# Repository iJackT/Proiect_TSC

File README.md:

OpenBook E-book Reader

Urmatorul fisier contine detalii despre implmentarea proiectului

Descriere generala
OpenBook este un e-reader open-source construit pe baza unui controller ESP32-C6. Acesta se foloseste de un ecran de 7.5" dar nu numai.

Diagrama Bloc:

Componente importante:

Microcontroller – ESP32-C6-WROOM-1
CPU: RISC-V pe 32 de biți, frecvență de 160 MHz
Memorie: 512 KB SRAM + 8 MB flash extern (model W25Q512JVEIQ)
Conectivitate: Suportă Wi-Fi 6 (802.11ax), Bluetooth 5 Low Energy, USB 2.0 Full-Speed

Ecran E-Ink – Waveshare WSH-13187, 7.5”
Rezoluție afișaj: 800x480 pixeli, alb-negru
Comunicare: Interfață SPI cu fire dedicate CS, DC, RST, BUSY
Consum de curent: Între 15–25 mA la reîmprospătare, consum nul în stare statică

Senzor ambiental – Bosch BME688
Măsurători: Temperatură, umiditate, presiune, calitate aer (eCO2, TVOC)
Precizie: ±1 °C (temperatură), ±3% (umiditate), ±1 hPa (presiune)
Comunicare: Protocol I²C @ 400 kHz

Alimentare și gestiunea energiei
Baterie: Li-Po 3.7V, capacitate 2500 mAh
Monitorizare baterie: MAX17048 (interfață I²C)
Încărcare: MCP73831, input 5V/1A prin conector USB-C

Interfață butoane – 3x switch tactil
Tip: Panasonic EVQ-Q2A03W
Legătură: GPIO cu debounce hardware (filtru RC)
Utilizare: Navigare în meniu, derulare pagini, confirmare acțiuni

Conector USB-C
Funcții: Încărcare baterie și transfer de date prin USB 2.0
Protecții: ESD și rezistențe de terminare corect configurate
Capabilități adiționale: Suport actualizări firmware prin USB și OTA prin Wi-Fi

Conector rapid I²C – Qwiic / STEMMA QT
Pini: VCC, GND, SDA, SCL
Rol: Permite conectarea ușoară a modulelor și senzorilor compatibili I²C

Slot MicroSD – Attend 112A-TAAR-R03
Scop: Permite stocarea externă de fișiere (cărți, jurnale, firmware)
Interfață: Conectare prin SPI

Ceas de timp real (RTC) – DS3231
Precizie: ±2 ppm
Interfață: I²C
Backup: Alimentare de rezervă prin supercapacitor

Pini folositi

| Pin ESP32-C6 | Componentă / Semnal                | De ce?                                                                 |
|--------------|-------------------------------------|------------------------------------------------------------------------|
| GPIO1        | I²C SDA (BME688, MAX17048, DS3231, Qwiic) | Linie partajată I²C – economisește pini și permite extinderea facilă |
| GPIO2        | I²C SCL (BME688, MAX17048, DS3231, Qwiic) | Clock I²C pentru toți senzorii și extensii Qwiic                     |
| GPIO5        | SPI MISO (E-Paper, Flash extern)    | Linie comună de intrare date în SPI                                   |
| GPIO6        | SPI MOSI (E-Paper, Flash extern)    | Linie de ieșire date către e-paper și flash                           |
| GPIO7        | SPI CLK                             | Semnal de clock pentru magistrala SPI                                 |
| GPIO8        | E-Paper CS                          | Selectează afișajul pe magistrala SPI                                 |
| GPIO9        | E-Paper DC (Data/Command)           | Comută între comandă și date către e-paper                            |
| GPIO10       | E-Paper RST                         | Reset hardware e-paper                                                |
| GPIO11       | E-Paper BUSY                        | Pin de stare (ocupat/liber) de la display                             |
| GPIO12       | Button #1                           | Intrare digitală pentru navigare pagină înainte                      |
| GPIO13       | Button #2                           | Intrare digitală pentru navigare pagină înapoi                       |
| GPIO14       | Button #3                           | Intrare digitală pentru selectare/opțiune                            |
| GPIO15       | MAX17048 ALERT (opțional)           | Pin de alertă nivel scăzut baterie                                    |
| GPIO16       | USB D+ (intern la USB PHY)          | Linie USB 2.0 (fixă pe ESP32-C6)                                      |
| GPIO17       | USB D- (intern la USB PHY)          | Linie USB 2.0 (fixă pe ESP32-C6)                                      |
| GPIO18       | LED Status (opțional)               | Indicator pentru activitate Wi-Fi, charging, notificări               |
| GPIO19       | SD Card CS                          | Selectare chip pentru card microSD (SPI)                              |
| GPIO20       | SD Card MISO                        | Citire date de pe card microSD                                        |
| GPIO21       | SD Card MOSI                        | Scriere date pe card microSD                                          |
| GPIO4        | SD Card CLK                         | Semnal de clock pentru card microSD (SPI)                             |

Comunicatii si Interfete

| Tip       | Componente                                          |
|-----------|-----------------------------------------------------|
| **SPI**   | E-Paper, Flash extern, SD Card (în mod SPI)         |
| **I²C**   | BME688, MAX17048, DS3231, Qwiic/Stemma              |
| **USB**   | Încărcare și transfer date prin USB-C               |
| **GPIO**  | Butoane, semnale control afișaj, charging enable    |

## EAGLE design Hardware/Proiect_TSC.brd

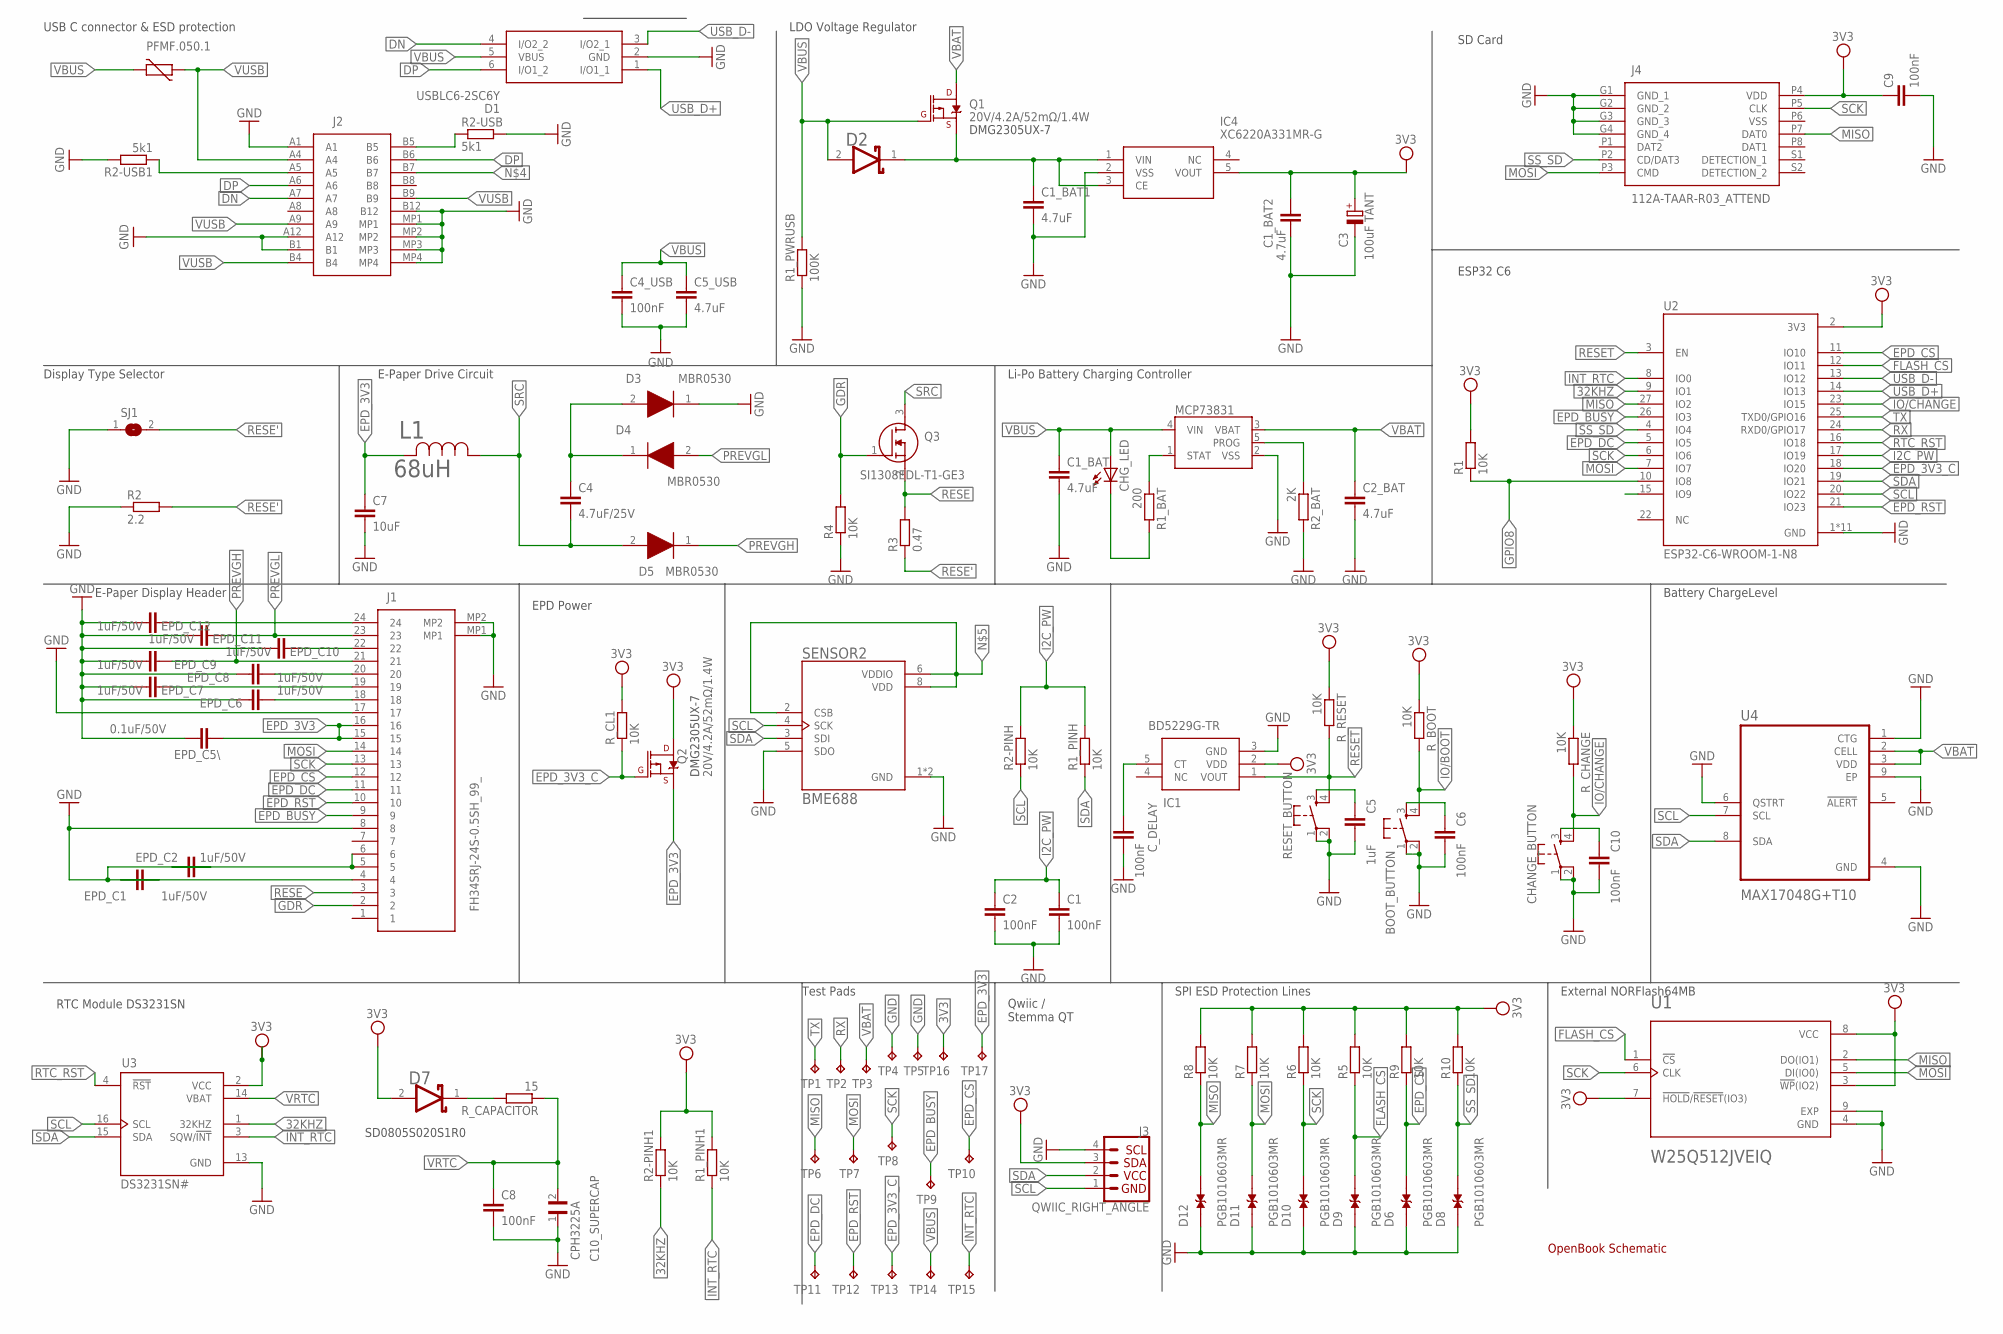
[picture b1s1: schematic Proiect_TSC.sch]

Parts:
BOOT_BUTTON: BUTTON_CUSYOMV1; MYBUTTON
C1, C2, C4_USB, C6, C8, C9, C10: 100nF; ESP32_WROVER_EAGLE-LTSPICE_C0402
C1_BAT, C1_BAT1, C1_BAT2, C2_BAT, C5_USB: 4.7uF; ESP32_WROVER_EAGLE-LTSPICE_C0402
C3: 100uF TANT; RCL_CT3528
C4: 4.7uF/25V; ESP32_WROVER_EAGLE-LTSPICE_C0402
C5: 1uF; ESP32_WROVER_EAGLE-LTSPICE_C0402
C7: 10uF; ESP32_WROVER_EAGLE-LTSPICE_C0402
C10_SUPERCAP: CPH3225A; CAPCP3225X100N
CHANGE_BUTTON: BUTTON_CUSYOMV1; MYBUTTON
CHG_LED: ADAFRUIT_LEDCHIP-LED0603; ADAFRUIT_CHIP-LED0603
C_DELAY: 100nF; ESP32_WROVER_EAGLE-LTSPICE_C0402
D1: USBLC6-2SC6Y; SOT95P280X145-6N
D2, D7: ESP32_WROVER_AVX---SD0805S020S1R0_AVX_SD0805S020S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; ESP32_WROVER_AVX---SD0805S020S1R0_AVX_SD0805S020S1R0_0
D3, D4, D5: MBR0530; SOD3716X135N
D6, D8, D9, D10, D11, D12: PGB1010603MR; DIOC1608X36N
EPD_C1, EPD_C2: 1uF/50V; ESP32_WROVER_EAGLE-LTSPICE_C0402
EPD_C5\: 0.1uF/50V; EAGLE-LTSPICE_C0402
EPD_C6, EPD_C7, EPD_C8, EPD_C9, EPD_C10, EPD_C11, EPD_C12: 1uF/50V; EAGLE-LTSPICE_C0402
IC1: BD5229G-TR; SOT95P280X125-5N
IC4: XC6220A331MR-G; SOT95P280X120-5N
J1: FH34SRJ-24S-0.5SH_99_; FH34SRJ24S05SH99
J2: SAMACSYS_PARTS_USB4110-GF-A; SAMACSYS_PARTS_USB4110GFA
J3: QWIIC_RIGHT_ANGLE; JST04_1MM_RA
J4: 112A-TAAR-R03_ATTEND; 112ATAARR03ATTEND
L1: 68uH; IND_4828-WE-TPC_WRE
MCP73831: ESP32_WROVER_SPARKFUN-IC-POWER_MCP73831; ESP32_WROVER_SPARKFUN-IC-POWER_SOT23-5
PFMF.050.1: ESP32C6_VARISTORCN1812; ESP32C6_VARISTOR_CT/CN1812
Q1, Q2: 20V/4.2A/52mΩ/1.4W; ESP32_WROVER_SPARKFUN-DISCRETESEMI_SOT23-3
Q3: SI1308EDL-T1-GE3; SOT65P210X110-3N
R1, R1_PINH, R1_PINH1, R2-PINH, R2-PINH1, R4, R5, R6, R7, R8, R9, R10: 10K; ESP32_WROVER_EAGLE-LTSPICE_R0402
R1_BAT: 200; ESP32_WROVER_EAGLE-LTSPICE_R0402
R1_PWRUSB: 100K; ESP32_WROVER_EAGLE-LTSPICE_R0402
R2: 2.2; ESP32_WROVER_EAGLE-LTSPICE_R0402
R2-USB, R2-USB1: 5k1; ESP32_WROVER_EAGLE-LTSPICE_R0402
R2_BAT: 2K; ESP32_WROVER_EAGLE-LTSPICE_R0402
R3: 0.47; ESP32_WROVER_EAGLE-LTSPICE_R0402
RESET_BUTTON: BUTTON_CUSYOMV1; MYBUTTON
R_BOOT: 10K; ESP32_WROVER_EAGLE-LTSPICE_R0402
R_CAPACITOR: 15; ESP32_WROVER_EAGLE-LTSPICE_R0402
R_CHANGE: 10K; ESP32_WROVER_EAGLE-LTSPICE_R0402
R_CL1: 10K; ESP32_WROVER_EAGLE-LTSPICE_R0402
R_RESET: 10K; ESP32_WROVER_EAGLE-LTSPICE_R0402
SENSOR2: BME688; ESP32_WROVER_BME680_PSON80P300X300X100-8N
SJ1: SJ
TP1, TP2, TP3, TP4, TP5, TP6, TP7, TP8, TP9, TP10, TP11, TP12, TP13, TP14, TP15, TP16, TP17: TPTP20R; TP20R
U1: W25Q512JVEIQ; SON127P600X800X80-9N
U2: ESP32-C6-WROOM-1-N8; XCVR_ESP32-C6-WROOM-1-N8
U3: DS3231SN#; SOIC127P1032X265-16N
U4: MAX17048G+T10; SON50P200X200X80-9N

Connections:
3V3: C1_BAT2.1, C3.+, C9.1, D7.2 (ANODE), IC1.2 (VDD), IC4.5 (VOUT), J3.3, J4.P4 (VDD), Q2.3 (D), R1.2, R1_PINH1.2, R2-PINH1.2, R5.2, R6.2, R7.2, R8.2, R9.2, R10.2, R_BOOT.1, R_CHANGE.1, R_CL1.2, R_RESET.1, TP16.TP, U1.3 (!WP!(IO2)), U1.7 (!HOLD!/!RESET!(IO3)), U1.8 (VCC), U2.2 (3V3), U3.2 (VCC)
32KHZ: R2-PINH1.1, U2.9 (IO1), U3.1 (32KHZ)
DN: D1.4 (I/O2_2), J2.A7
DP: D1.6 (I/O1_2), J2.A6, J2.B6
EPD_3V3: C7.1, EPD_C5\.1, J1.15, J1.16, L1.2, Q2.2 (S), TP17.TP
EPD_3V3_C: Q2.1 (G), R_CL1.1, TP13.TP, U2.18 (IO20)
EPD_BUSY: J1.9, TP9.TP, U2.26 (IO3)
EPD_C2: EPD_C2.2, J1.5, J1.6
EPD_CS: D6.2, J1.12, R9.1, TP10.TP, U2.11 (IO10)
EPD_DC: J1.11, TP11.TP, U2.5 (IO5)
EPD_RST: J1.10, TP12.TP, U2.21 (IO23)
FLASH_CS: D9.2, R5.1, U1.1 (!CS), U2.12 (IO11)
GDR: J1.2, Q3.1 (G), R4.2
GND: BOOT_BUTTON.2, C1.2, C1_BAT.2, C1_BAT1.2, C1_BAT2.2, C2.2, C2_BAT.2, C3.-, C4_USB.2, C5.2, C5_USB.2, C6.2, C7.2, C8.2, C9.2, C10.2, C10_SUPERCAP.1, CHANGE_BUTTON.2, C_DELAY.2, D1.2 (GND), D3.1 (K), D6.1, D8.1, D9.1, D10.1, D11.1, D12.1, EPD_C1.1, EPD_C2.1, EPD_C5\.2, EPD_C6.2, EPD_C7.2, EPD_C8.2, EPD_C9.2, EPD_C10.2, EPD_C11.2, EPD_C12.2, IC1.3 (GND), IC4.2 (VSS), J1.8, J1.17, J1.MP1, J1.MP2, J2.A1, J2.A12, J2.B1, J2.B12, J2.MP1, J2.MP2, J2.MP3, J2.MP4, J3.4, J4.G1 (GND_1), J4.G2 (GND_2), J4.G3 (GND_3), J4.G4 (GND_4), MCP73831.2 (VSS), R1_PWRUSB.1, R2.1, R2-USB.2, R2-USB1.2, R2_BAT.2, R4.1, RESET_BUTTON.1, RESET_BUTTON.2, SENSOR2.1 (GND), SENSOR2.5 (SDO), SENSOR2.7 (GND), SJ1.1, TP4.TP, TP5.TP, U1.4 (GND), U1.9 (EXP), U2.1 (GND), U2.28 (GND), U2.29_1 (GND), U2.29_2 (GND), U2.29_3 (GND), U2.29_4 (GND), U2.29_5 (GND), U2.29_6 (GND), U2.29_7 (GND), U2.29_8 (GND), U2.29_9 (GND), U3.13 (GND), U4.1 (CTG), U4.4 (GND), U4.6 (QSTRT), U4.9 (EP)
GPIO8: R1.1, U2.10 (IO8)
I2C_PW: C1.1, C2.1, R1_PINH.2, R2-PINH.2, U2.17 (IO19)
INT_RTC: R1_PINH1.1, TP15.TP, U2.8 (IO0), U3.3 (SQW/!INT)
IO/BOOT: BOOT_BUTTON.4, R_BOOT.2
IO/CHANGE: CHANGE_BUTTON.4, R_CHANGE.2, U2.23 (IO15)
MISO: D12.2, J4.P7 (DAT0), R8.1, TP6.TP, U1.2 (DO(IO1)), U2.27 (IO2)
MOSI: D11.2, J1.14, J4.P3 (CMD), R7.1, TP7.TP, U1.5 (DI(IO0)), U2.7 (IO7)
unnamed: J2.A5, R2-USB1.1
unnamed: J2.B5, R2-USB.1
unnamed: C1_BAT1.1, D2.1 (CATHODE), IC4.1 (VIN), IC4.3 (CE), Q1.2 (S)
unnamed: SENSOR2.2 (CSB), SENSOR2.6 (VDDIO), SENSOR2.8 (VDD)
unnamed: MCP73831.5 (PROG), R2_BAT.1
unnamed: C4.1, D3.2 (A), D4.1 (K)
unnamed: C_DELAY.1, IC1.5 (CT)
unnamed: EPD_C1.2, J1.4
unnamed: MCP73831.1 (STAT), R1_BAT.1
unnamed: CHG_LED.C, R1_BAT.2
unnamed: EPD_C6.1, J1.18
unnamed: EPD_C7.1, J1.19
unnamed: EPD_C8.1, J1.20
unnamed: D7.1 (CATHODE), R_CAPACITOR.2
unnamed: EPD_C10.1, J1.22
unnamed: BOOT_BUTTON.3, C6.1
unnamed: EPD_C12.1, J1.24
unnamed: C5.1, RESET_BUTTON.3
unnamed: C10.1, CHANGE_BUTTON.3
PREVGH: D5.1 (K), EPD_C9.1, J1.21
PREVGL: D4.2 (A), EPD_C11.1, J1.23
RESE: J1.3, Q3.2 (S), R3.2
RESE': R2.2, R3.1, SJ1.2
RESET: IC1.1 (VOUT), RESET_BUTTON.4, R_RESET.2, U2.3 (EN)
RTC_RST: U2.16 (IO18), U3.4 (!RST)
RX: TP2.TP, U2.24 (RXD0/GPIO17)
SCK: D10.2, J1.13, J4.P5 (CLK), R6.1, TP8.TP, U1.6 (CLK), U2.6 (IO6)
SCL: J3.1, R2-PINH.1, SENSOR2.4 (SCK), U2.20 (IO22), U3.16 (SCL), U4.7 (SCL)
SDA: J3.2, R1_PINH.1, SENSOR2.3 (SDI), U2.19 (IO21), U3.15 (SDA), U4.8 (SDA)
SRC: C4.2, D5.2 (A), L1.1, Q3.3 (D)
SS_SD: D8.2, J4.P2 (CD/DAT3), R10.1, U2.4 (IO4)
TX: TP1.TP, U2.25 (TXD0/GPIO16)
USB_D+: D1.1 (I/O1_1), U2.14 (IO13)
USB_D-: D1.3 (I/O2_1), U2.13 (IO12)
VBAT: C2_BAT.1, MCP73831.3 (VBAT), Q1.3 (D), TP3.TP, U4.2 (CELL), U4.3 (VDD)
VBUS: C1_BAT.1, C4_USB.1, C5_USB.1, CHG_LED.A, D1.5 (VBUS), D2.2 (ANODE), MCP73831.4 (VIN), PFMF.050.1.2, Q1.1 (G), R1_PWRUSB.2, TP14.TP
VRTC: C8.1, C10_SUPERCAP.2, R_CAPACITOR.1, U3.14 (VBAT)
VUSB: J2.A4, J2.A9, J2.B4, J2.B9, PFMF.050.1.1

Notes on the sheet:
USB C connector & ESD protection
DMG2305UX-7
LDO Voltage Regulator
SD Card
Display Type Selector
E-Paper Drive Circuit
Li-Po Battery Charging Controller
ESP32 C6
EPD Power
Battery ChargeLevel
E-Paper Display Header
SD0805S020S1R0
RTC Module DS3231SN
Test Pads
Qwiic / Stemma QT
SPI ESD Protection Lines
OpenBook Schematic
External NORFlash64MB

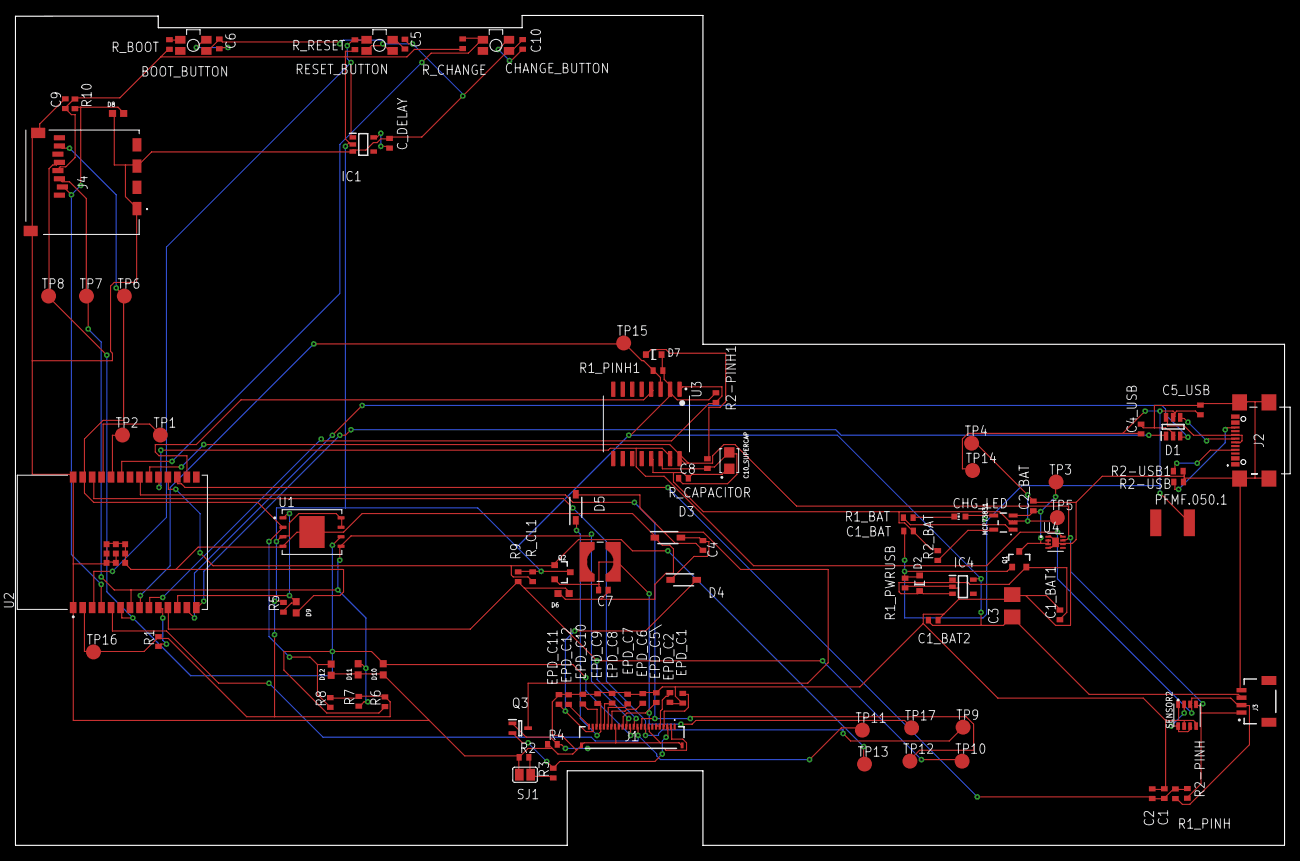
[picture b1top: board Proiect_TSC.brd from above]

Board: 2 copper layers, 170.2 x 111.3 mm, 103 parts (0 on the bottom side), 59 nets.

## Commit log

2025-04-09 Create schematic
2025-04-09 Rename Proiect_TSC_sch.sch to Proiect_TSC.sch
2025-04-09 Create file
2025-04-12 Create LICENSE
2025-04-15 Create t
2025-04-15 Create m

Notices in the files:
parts and their libraries:
COPYRIGHT: Copyright (C) 2024 Ultra Librarian. All rights reserved.
